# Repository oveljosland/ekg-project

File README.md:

# EKG Hardware Project

⚠️ Note: This project is a work in progress. Features and documentation may change frequently.

## Overview
This repository contains the design and documentation files for an EKG hardware project in an Electronics Design course. The project includes schematics, PCB layouts, useful scripts, and other design resources created using **KiCad**.

## Features
- **Modular design**: Allows easy modifications and improvements.
- **Open-source**: All design files and documentation are freely available.

## Repository Contents
- `ekg-interface/`- Design files for the EKG interface.
- `step-down/` - Design files for the step-down converter.

## Schematics
### EKG Interface

### Step-Down Converter

## Tools Used
- **KiCad** - Open-source PCB design tool.
- **LTspice** - Circuit simulation.

## Getting Started
1. Clone this repository:
   ```sh
   git clone https://github.com/oveljosland/ekg-project.git
   ```
2. Open the schematics in **KiCad** or other EDA software.
3. Modify and generate PCB layout as needed.
4. Export Gerber files and fabricate the PCB.
5. Assemble and test!

## License
This project is licensed under the **MIT License**. See [LICENSE](LICENSE) for details.

## Contact
For questions or feedback, feel free to reach out via [GitHub Issues](https://github.com/oveljosland/ekg-project/issues).

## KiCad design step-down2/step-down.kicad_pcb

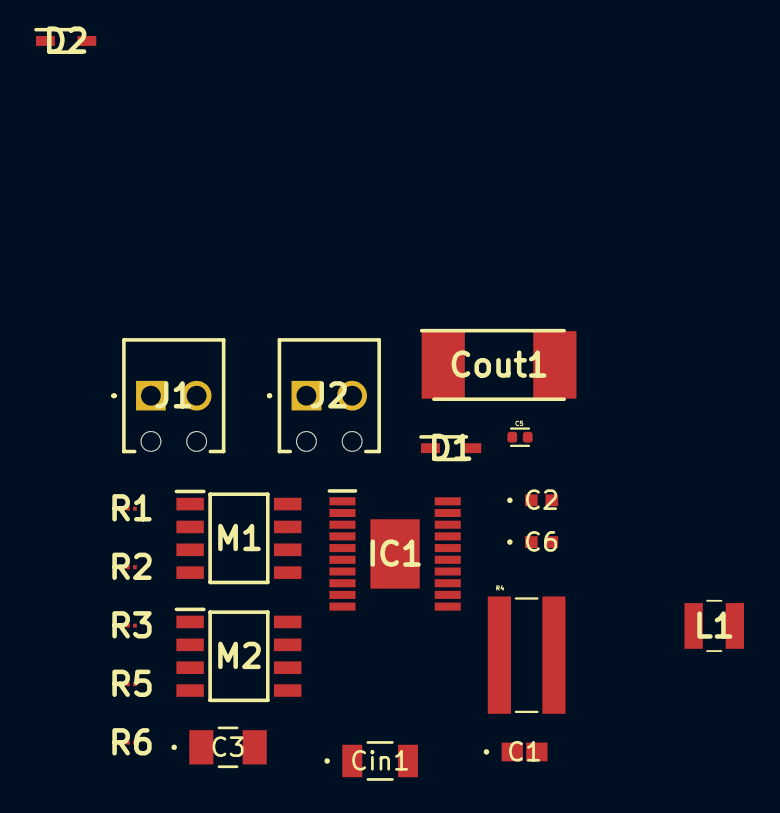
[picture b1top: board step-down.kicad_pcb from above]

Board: 2 copper layers, 21 parts (0 on the bottom side), 18 nets, no tracks yet.

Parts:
C1: 4n7; CAP_CS0603_YAG
C2, C6: 0u1; CAP_CS0402_YAG
C3: 47p; CAP_CS1206_YAG
C5: 2u2; CC0402KRX5R7BB225
Cin1: 22u; CAP_CC1206_YAG
Cout1: 150u; TAZH157J010LBSZ0H00
D1, D2: CMDSH2-3; CMDSH2-3_TR_PBFREE
IC1: LTC3807EFE#PBF
J1, J2: Screw_Terminal_01x02; 1725656
L1: 10u; AISC-1008F-100G-T
M1, M2: IRF7413ZPBF
R1: 15k4; ERJ-XGNF1542Y
R2: 60k4; ERJ-XGNF6042Y
R3, R5: 100k; ERJ-XGNF1003Y
R4: 4m; KRL6432D-C-R004-F-T5
R6: 400k; ERJ-XGNF4023Y

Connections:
GND: C1.1, C2.1, C3.2, C5.2, Cin1.2, Cout1.2, D2.2 (A), IC1.17 (EXTVCC), IC1.18 (PGND), J1.1, J2.1, M2.1 (S_1), M2.2 (S_2), M2.3 (S_3), R2.1, R6.2
GNDS: IC1.4 (SGND_1), IC1.5 (SGND_2), IC1.21 (SGND_3)
unnamed: C1.2, R1.1
unnamed: C5.1, D1.2 (A), IC1.16 (INTVCC), R3.1
unnamed: C6.1, D1.1 (K), IC1.14 (BOOST)
unnamed: C6.2, D2.1 (K), IC1.13 (SW), L1.1, M1.1 (S_1), M1.2 (S_2), M1.3 (S_3), M2.5 (D_1)
unnamed: IC1.15 (BG), M2.4 (G)
unnamed: IC1.2 (FREQ), R2.2
unnamed: C3.1, IC1.10 (ITH), R1.2
unnamed: IC1.11 (PGOOD), R3.2
unnamed: IC1.8 (SENSE+), L1.2, R4.1
unnamed: Cout1.1, IC1.7 (SENSE-), J2.2, R4.2, R5.1
unnamed: IC1.12 (TG), M1.4 (G)
unnamed: C2.2, IC1.1 (TRACK/SS)
unnamed: IC1.9 (VFB), R5.2, R6.1
unnamed: Cin1.1, IC1.19 (VIN), J1.2, M1.5 (D_1)
unnamed: M1.6 (D_2), M1.7 (D_3), M1.8 (D_4)
unnamed: M2.6 (D_2), M2.7 (D_3), M2.8 (D_4)

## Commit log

2025-02-10 init
2025-02-11 added ekg interfacing circuit
2025-02-11 readme
2025-02-11 Create LICENSE
2025-02-11 step-down
2025-02-11 cleanup
2025-02-11 images
2025-02-12 set components
2025-02-12 added components
2025-02-12 formattin
2025-02-12 formatting
2025-02-12 assigned footprints
2025-02-12 assigned footprint L1: Bourns SRP6060FA
2025-02-12 v1.1
2025-02-12 add pcb
2025-02-12 small change
2025-02-14 Add files via upload
    beep boop
2025-02-14 add new lib
2025-02-14 added v2 to step-down2/
2025-02-14 fixed mosfet connections
2025-02-14 gnd fix
2025-02-14 fixed dup folder
2025-02-14 fixed ERC error
2025-02-14 fixed all ERC errors
2025-02-16 drill,gerber,bom
2025-02-16 new version
2025-02-16 added images and shc, pcb to submissions
